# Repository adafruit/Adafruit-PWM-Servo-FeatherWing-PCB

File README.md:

## Adafruit PWM Servo FeatherWing PCB
<a href="http://www.adafruit.com/products/2928"><br/>
Click here to purchase one from the Adafruit shop</a>

This is the 8-Channel PWM or Servo​ FeatherWing, you can add 8 x 12-bit PWM outputs to your Feather board. Using our Feather Stacking Headers or Feather Female Headers you can connect a FeatherWing on top or bottom of your Feather board and let the board take flight!

You want to make a cool robot, maybe a hexapod walker, or maybe just a piece of art with a lot of moving parts. Or maybe you want to drive a lot of LEDs with precise PWM output. What now? You could give up OR you could just get our handy PWM and Servo FeatherWing. It's a lot like our popular PWM/Servo Shield but with half the channels & squished into a nice small portable size and works with any of our Feather boards.

This is the PCB for the PCB files for the Adafruit PWM Servo FeatherWing. The format is EagleCAD schematic and board layout
- https://www.adafruit.com/products/2928

### License

Adafruit invests time and resources providing this open source design, please support Adafruit and open-source hardware by purchasing products from [Adafruit](https://www.adafruit.com)!

All text above must be included in any redistribution

Designed by Limor Fried/Ladyada for Adafruit Industries.
Creative Commons Attribution/Share-Alike, all text above must be included in any redistribution. 
See license.txt for additional information.

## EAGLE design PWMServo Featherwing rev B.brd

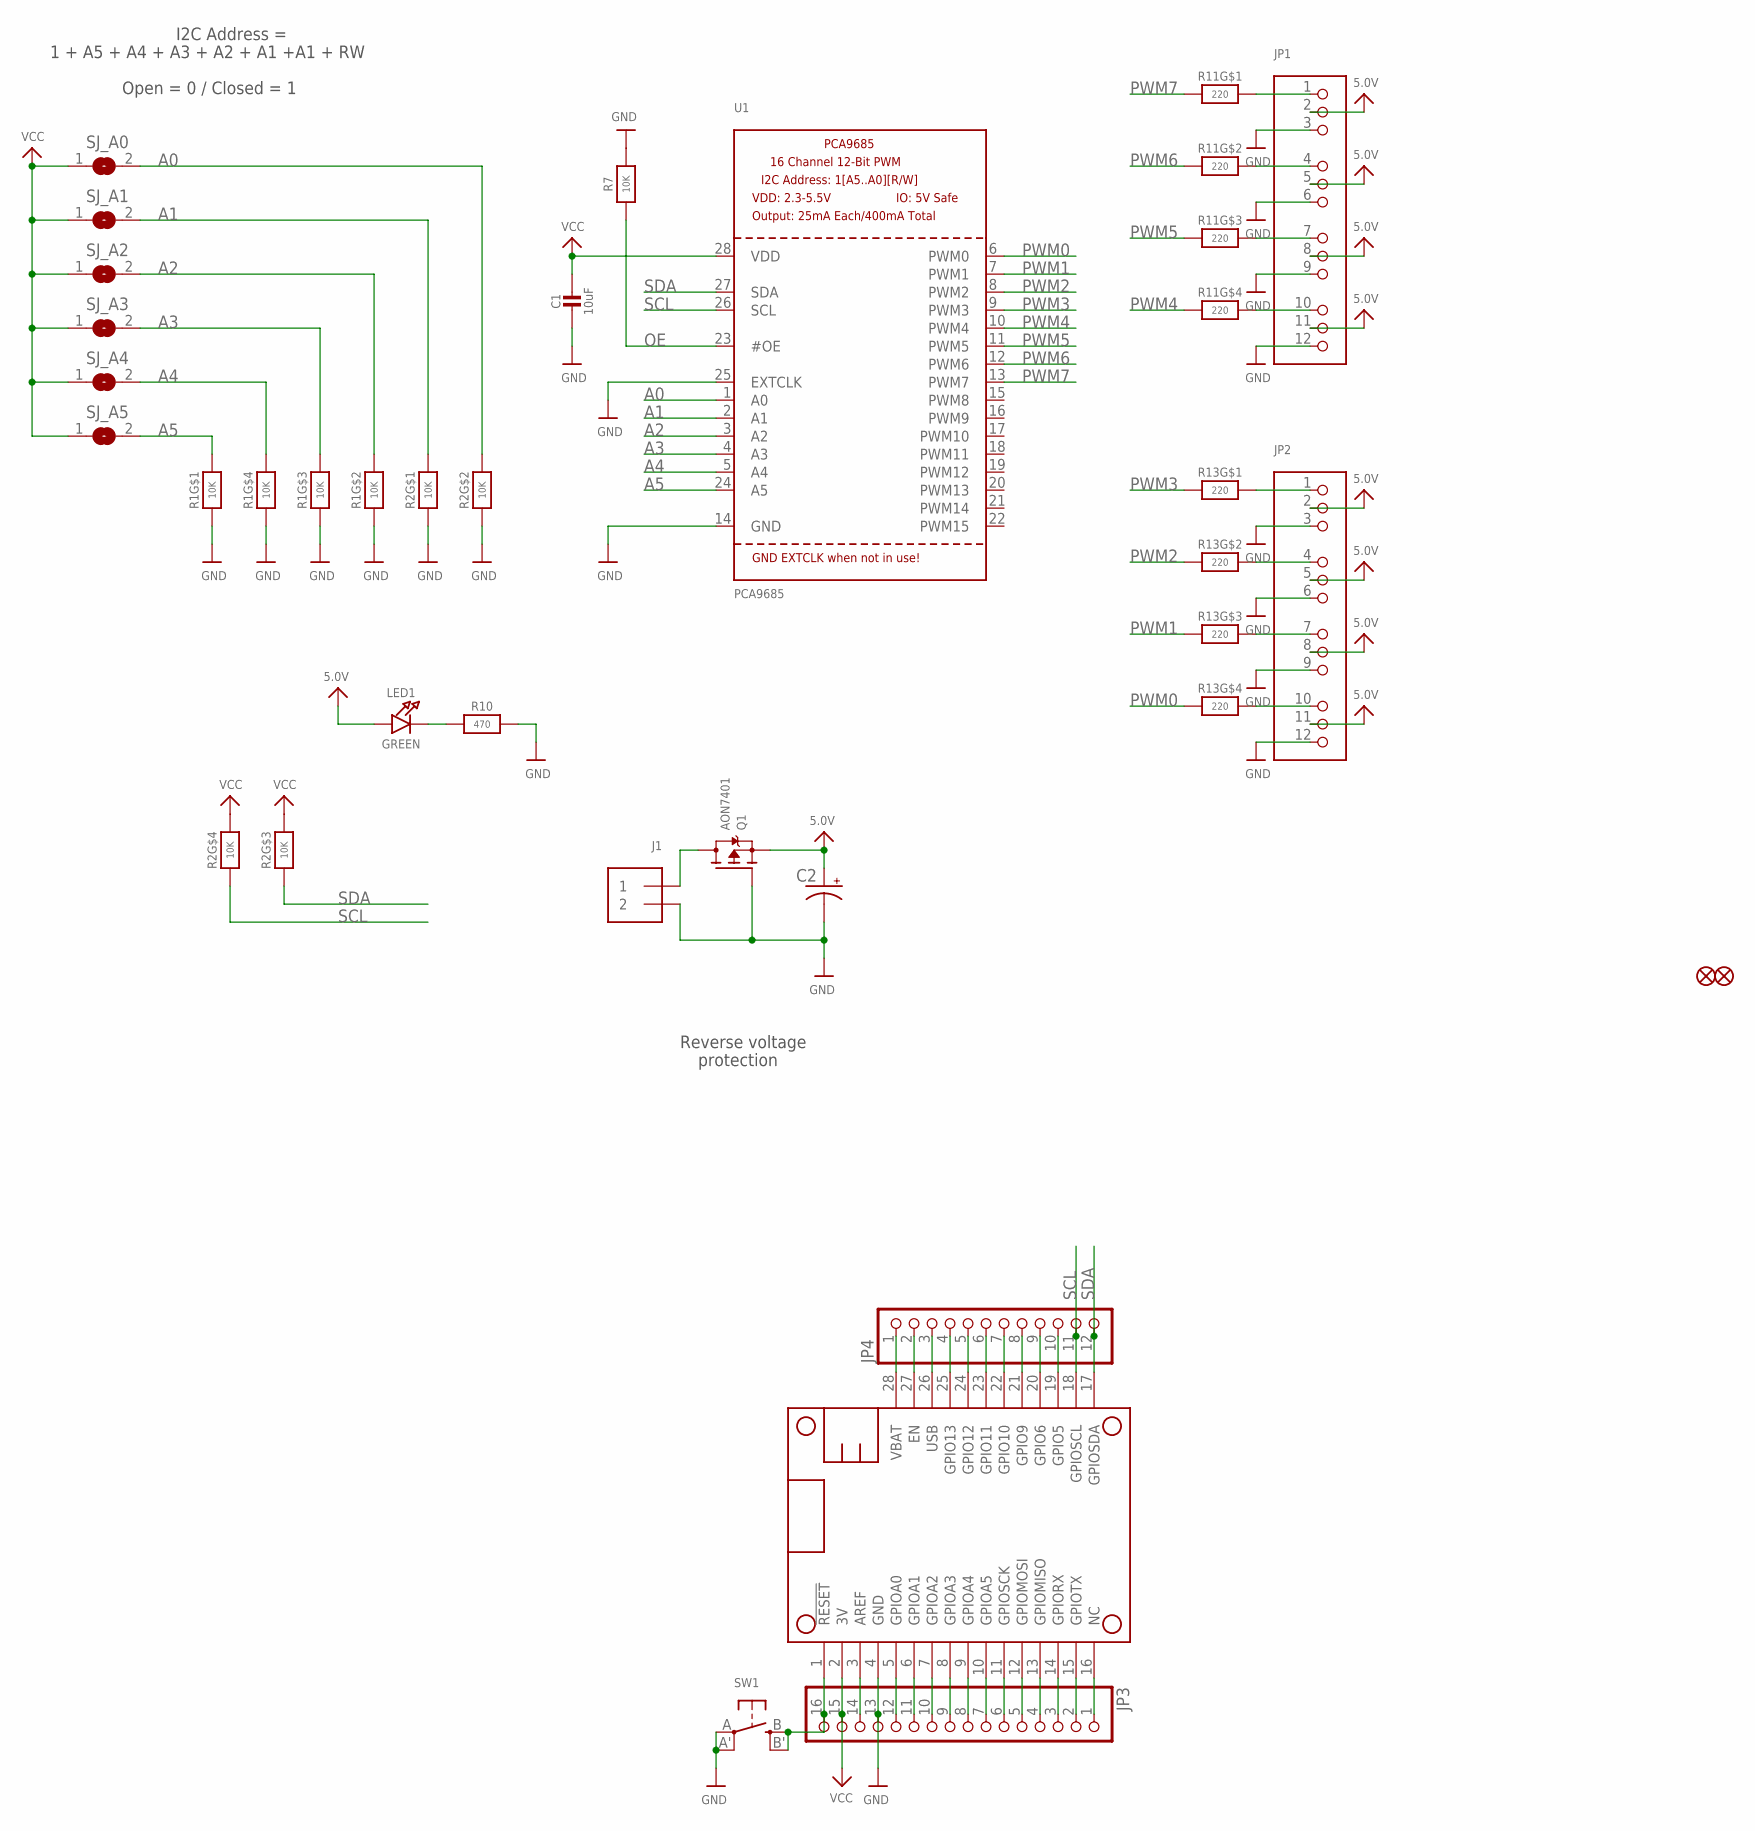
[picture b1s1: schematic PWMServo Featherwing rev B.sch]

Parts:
C1: 10uF; 0805-NO
C2: CPOL-USE3.5-8; E3,5-8
FID1, FID2: FIDUCIAL""; FIDUCIAL_1MM
J1: TERMBLOCK_1X2; TERMBLOCK_1X2-3.5MM
JP1, JP2: HEADER-3X04; 3X04
JP3: HEADER-1X16ROUND; 1X16_ROUND
JP4: HEADER-1X12; 1X12_ROUND
LED1: GREEN; CHIPLED_0805_NOOUTLINE
MS1: FEATHERWING
Q1: AON7401; POWERDI3333
R1, R2: 10K; RESPACK_4X0603
R7: 10K; 0805-NO
R10: 470; 0805-NO
R11, R13: 220; RESPACK_4X0603
SJ_A0, SJ_A1, SJ_A2, SJ_A3, SJ_A4, SJ_A5: SOLDERJUMPERREFLOW_NOPASTE; SOLDERJUMPER_REFLOW_NOPASTE
SW1: SWITCH_TACT_SMT4.6X2.8; BTN_KMR2_4.6X2.8
U1: PCA9685; TSSOP28

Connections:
5.0V: C2.+, JP1.2, JP1.5, JP1.8, JP1.11, JP2.2, JP2.5, JP2.8, JP2.11, LED1.A, Q1.1 (S), Q1.2 (S), Q1.3 (S)
A0: R2.7 (2), SJ_A0.2, U1.1 (A0)
A1: R2.8 (2), SJ_A1.2, U1.2 (A1)
A2: R1.7 (2), SJ_A2.2, U1.3 (A2)
A3: R1.6 (2), SJ_A3.2, U1.4 (A3)
A4: R1.5 (2), SJ_A4.2, U1.5 (A4)
A5: R1.8 (2), SJ_A5.2, U1.24 (A5)
GND: C1.2, C2.-, J1.2, JP1.3, JP1.6, JP1.9, JP1.12, JP2.3, JP2.6, JP2.9, JP2.12, JP3.13, MS1.4 (GND), Q1.4 (G), R1.1, R1.2 (1), R1.3 (1), R1.4 (1), R2.1, R2.2 (1), R7.2, R10.2, SW1.A, SW1.A' (P1), U1.14 (GND), U1.25 (EXTCLK)
unnamed: LED1.C, R10.1
unnamed: JP1.4, R11.7 (2)
unnamed: JP1.1, R11.8 (2)
unnamed: JP1.7, R11.6 (2)
unnamed: JP1.10, R11.5 (2)
unnamed: JP2.1, R13.8 (2)
unnamed: JP2.4, R13.7 (2)
unnamed: JP2.7, R13.6 (2)
unnamed: JP2.10, R13.5 (2)
unnamed: JP3.1, MS1.16 (NC)
unnamed: JP3.2, MS1.15 (GPIOTX)
unnamed: JP3.3, MS1.14 (GPIORX)
unnamed: JP3.4, MS1.13 (GPIOMISO)
unnamed: JP3.5, MS1.12 (GPIOMOSI)
unnamed: JP3.6, MS1.11 (GPIOSCK)
unnamed: JP3.7, MS1.10 (GPIOA5)
unnamed: JP3.8, MS1.9 (GPIOA4)
unnamed: JP3.9, MS1.8 (GPIOA3)
unnamed: JP3.10, MS1.7 (GPIOA2)
unnamed: JP3.11, MS1.6 (GPIOA1)
unnamed: JP3.12, MS1.5 (GPIOA0)
unnamed: JP3.14, MS1.3 (AREF)
unnamed: JP4.2, MS1.27 (EN)
unnamed: JP4.4, MS1.25 (GPIO13)
unnamed: JP4.5, MS1.24 (GPIO12)
unnamed: JP4.6, MS1.23 (GPIO11)
unnamed: JP4.7, MS1.22 (GPIO10)
unnamed: JP4.8, MS1.21 (GPIO9)
unnamed: JP4.9, MS1.20 (GPIO6)
unnamed: JP4.10, MS1.19 (GPIO5)
unnamed: JP3.16, MS1.1 (!RESET), SW1.B (S), SW1.B' (S1)
OE: R7.1, U1.23 (#OE)
PWM0: R13.4 (1), U1.6 (PWM0)
PWM1: R13.3 (1), U1.7 (PWM1)
PWM2: R13.2 (1), U1.8 (PWM2)
PWM3: R13.1, U1.9 (PWM3)
PWM4: R11.4 (1), U1.10 (PWM4)
PWM5: R11.3 (1), U1.11 (PWM5)
PWM6: R11.2 (1), U1.12 (PWM6)
PWM7: R11.1, U1.13 (PWM7)
PWRIN: J1.1, Q1.5678 (D)
SCL: JP4.11, MS1.18 (GPIOSCL), R2.4 (1), U1.26 (SCL)
SDA: JP4.12, MS1.17 (GPIOSDA), R2.3 (1), U1.27 (SDA)
USB: JP4.3, MS1.26 (USB)
VBAT: JP4.1, MS1.28 (VBAT)
VCC: C1.1, JP3.15, MS1.2 (3V), R2.5 (2), R2.6 (2), SJ_A0.1, SJ_A1.1, SJ_A2.1, SJ_A3.1, SJ_A4.1, SJ_A5.1, U1.28 (VDD)

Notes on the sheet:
Reverse voltage
protection
1 + A5 + A4 + A3 + A2 + A1 +A1 + RW
I2C Address =
Open = 0 / Closed = 1

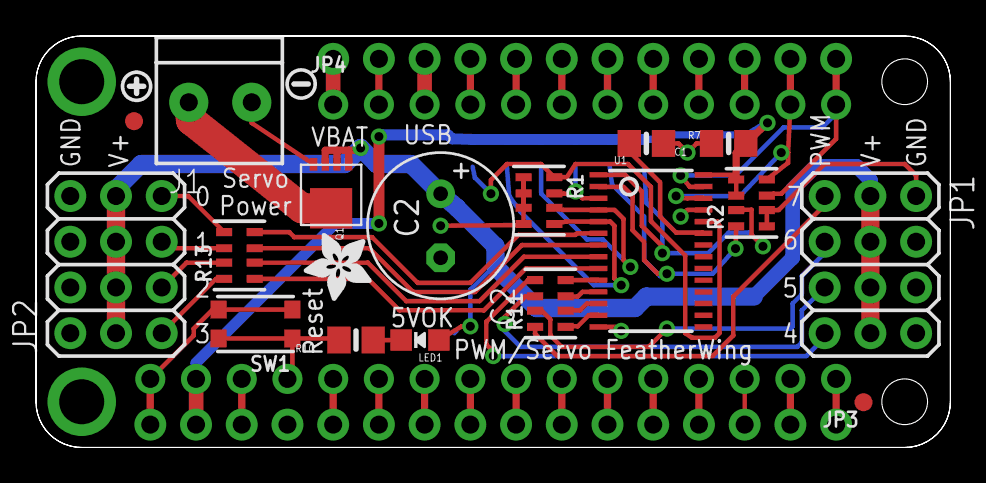
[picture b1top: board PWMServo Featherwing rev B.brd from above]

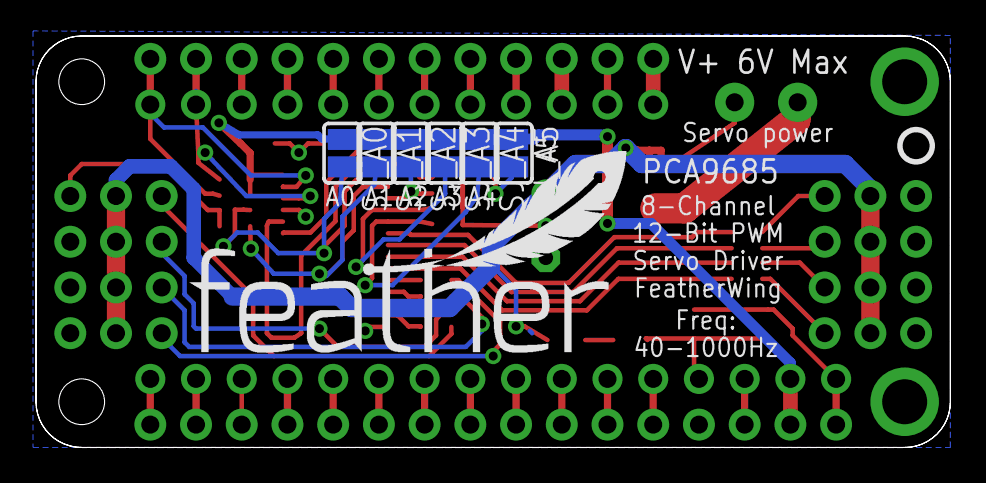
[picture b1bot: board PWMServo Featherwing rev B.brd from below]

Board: 2 copper layers, 50.8 x 22.9 mm, 31 parts (8 on the bottom side), 54 nets.

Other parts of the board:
U$11: SYMBOL_PLUS
U$12: SYMBOL_MINUS
U$14: ADAFRUIT_3.5MM
U$15: FEATHERLOGO
U$16: PCBFEAT-REV-040

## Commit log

2016-03-01 init
2016-03-01 fix url
